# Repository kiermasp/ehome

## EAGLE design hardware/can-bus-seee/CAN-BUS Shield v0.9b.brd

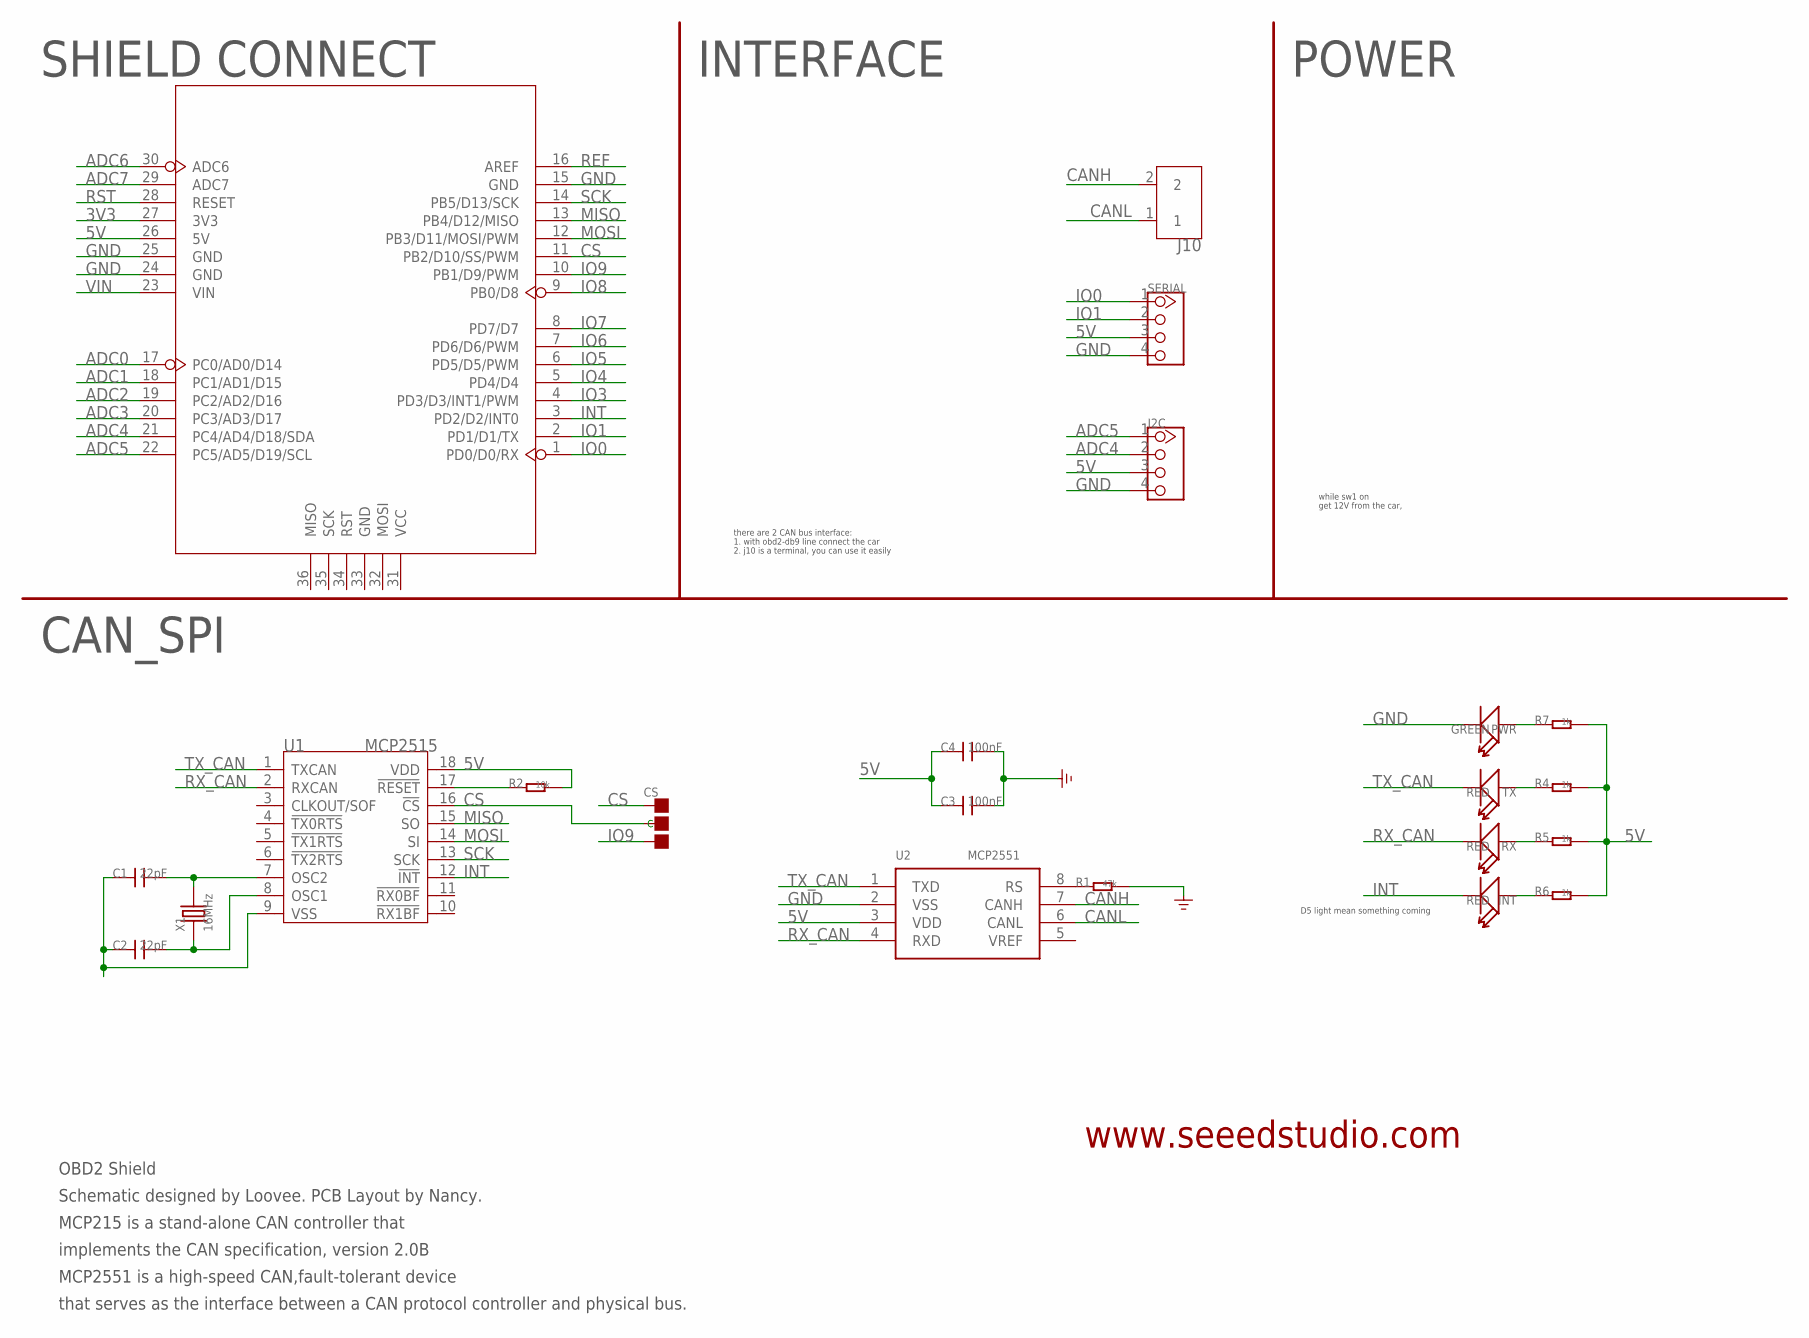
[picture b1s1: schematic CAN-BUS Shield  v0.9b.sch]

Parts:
C1, C2: 22pF; 0603
C3, C4: 100nF; 0603
CS: PAD-JUMPER-3P-40*40; 3P-SMD-4.1X1.5
I2C: TWIG-4P-2.0-2.0; 4P-2.0
INT: RED; LED-0603
J10: SCREW-TERMINAL-2P5.0; 2P-5.0
PWR: GREEN; LED-0603
R1: 47k; 0603
R2: 10k; 0603
R4, R5, R6, R7: 1k; 0603
RX: RED; LED-0603
SERIAL: TWIG-4P-2.0-2.0; 4P-2.0
TX: RED; LED-0603
U1: MCP2515; SOIC18
U2: MCP2551; SO08
U3: ARDUINO
X1: 16MHz; HC49/S

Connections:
3V3: U3.27 (3V3)
5V: C3.1, C4.1, I2C.3, R2.2, R4.2, R5.2, R6.2, R7.2, SERIAL.3, U1.18 (VDD), U2.3 (VDD), U3.26 (5V)
ADC0: U3.17 (PC0/AD0/D14)
ADC1: U3.18 (PC1/AD1/D15)
ADC2: U3.19 (PC2/AD2/D16)
ADC3: U3.20 (PC3/AD3/D17)
ADC4: I2C.2, U3.21 (PC4/AD4/D18/SDA)
ADC5: I2C.1, U3.22 (PC5/AD5/D19/SCL)
ADC6: U3.30 (ADC6)
ADC7: U3.29 (ADC7)
CANH: J10.2, U2.7 (CANH)
CANL: J10.1, U2.6 (CANL)
CS: CS.00 (L), CS.MM (C), U1.16 (!CS), U3.11 (PB2/D10/SS/PWM)
INT: INT.-, U1.12 (!INT), U3.3 (PD2/D2/INT0)
IO0: SERIAL.1, U3.1 (PD0/D0/RX)
IO1: SERIAL.2, U3.2 (PD1/D1/TX)
IO3: U3.4 (PD3/D3/INT1/PWM)
IO4: U3.5 (PD4/D4)
IO5: U3.6 (PD5/D5/PWM)
IO6: U3.7 (PD6/D6/PWM)
IO7: U3.8 (PD7/D7)
IO8: U3.9 (PB0/D8)
IO9: CS.11 (R), U3.10 (PB1/D9/PWM)
MISO: U1.15 (SO), U3.13 (PB4/D12/MISO)
MOSI: U1.14 (SI), U3.12 (PB3/D11/MOSI/PWM)
unnamed: PWR.+, R7.1
unnamed: R4.1, TX.+
unnamed: R5.1, RX.+
unnamed: C1.2, U1.7 (OSC2), X1.2
unnamed: C2.2, U1.8 (OSC1), X1.1
unnamed: INT.+, R6.1
unnamed: R1.1, U2.8 (RS)
REF: U3.16 (AREF)
RST: U3.28 (RESET)
RST_N: R2.1, U1.17 (!RESET)
RX_CAN: RX.-, U1.2 (RXCAN), U2.4 (RXD)
SCK: U1.13 (SCK), U3.14 (PB5/D13/SCK)
TX_CAN: TX.-, U1.1 (TXCAN), U2.1 (TXD)
VIN: U3.23 (VIN)

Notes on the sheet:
CAN_SPI
SHIELD CONNECT
INTERFACE
POWER
get 12V from the car,
D5 light mean something coming
OBD2 Shield
Schematic designed by Loovee. PCB Layout by Nancy.
MCP215 is a stand-alone CAN controller that
MCP2551 is a high-speed CAN,fault-tolerant device
that serves as the interface between a CAN protocol controller and physical bus.
implements the CAN specification, version 2.0B
www.seeedstudio.com
while sw1 on
there are 2 CAN bus interface:
1. with obd2-db9 line connect the car
2. j10 is a terminal, you can use it easily

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
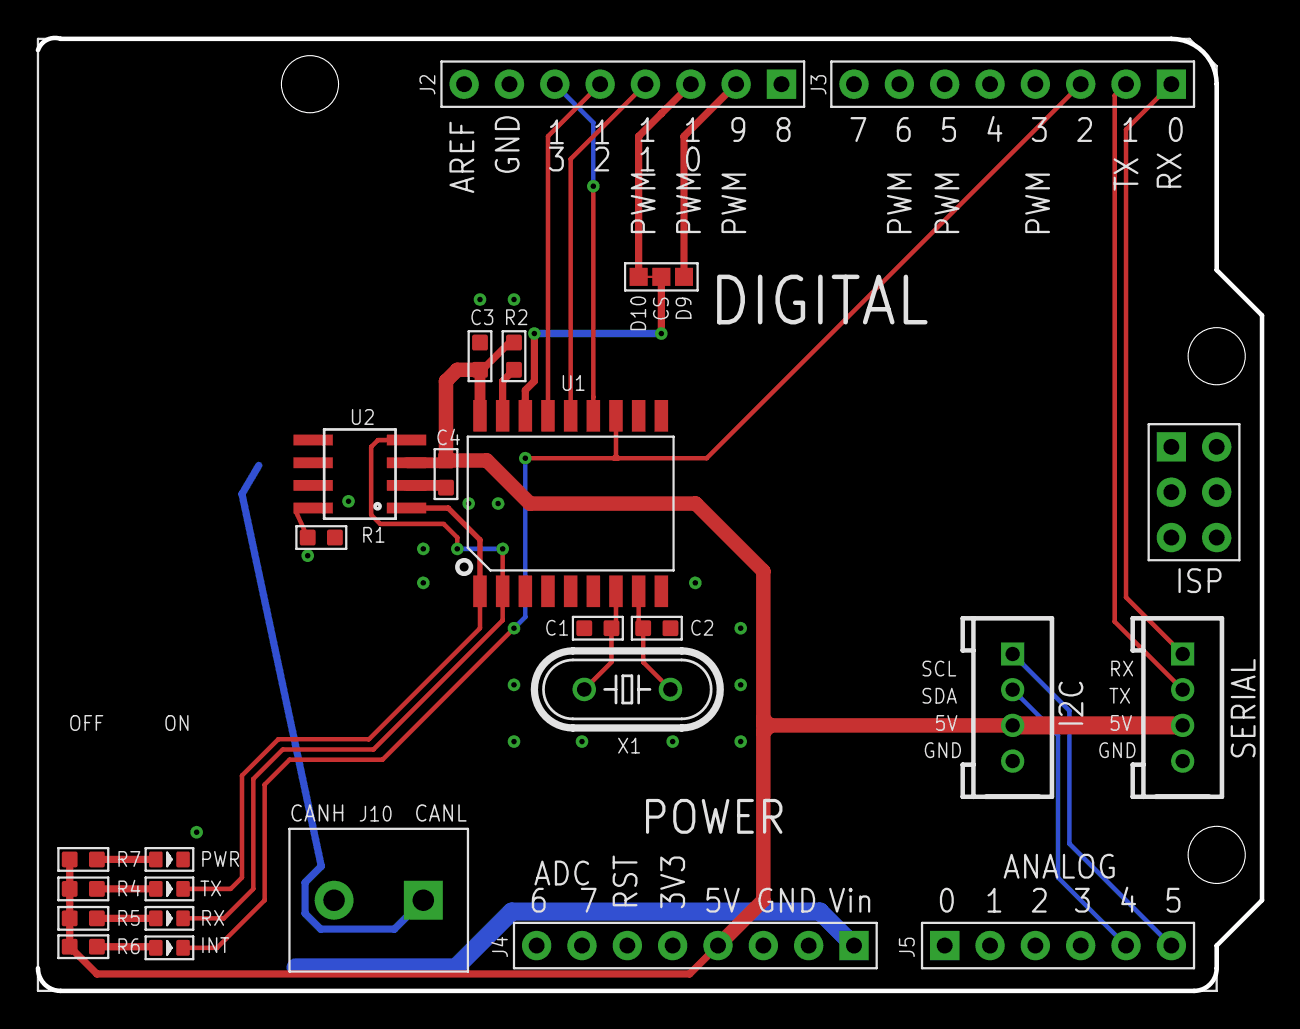
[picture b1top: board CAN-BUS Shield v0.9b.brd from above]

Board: 2 copper layers, 68.6 x 53.4 mm, 22 parts (0 on the bottom side), 24 nets.

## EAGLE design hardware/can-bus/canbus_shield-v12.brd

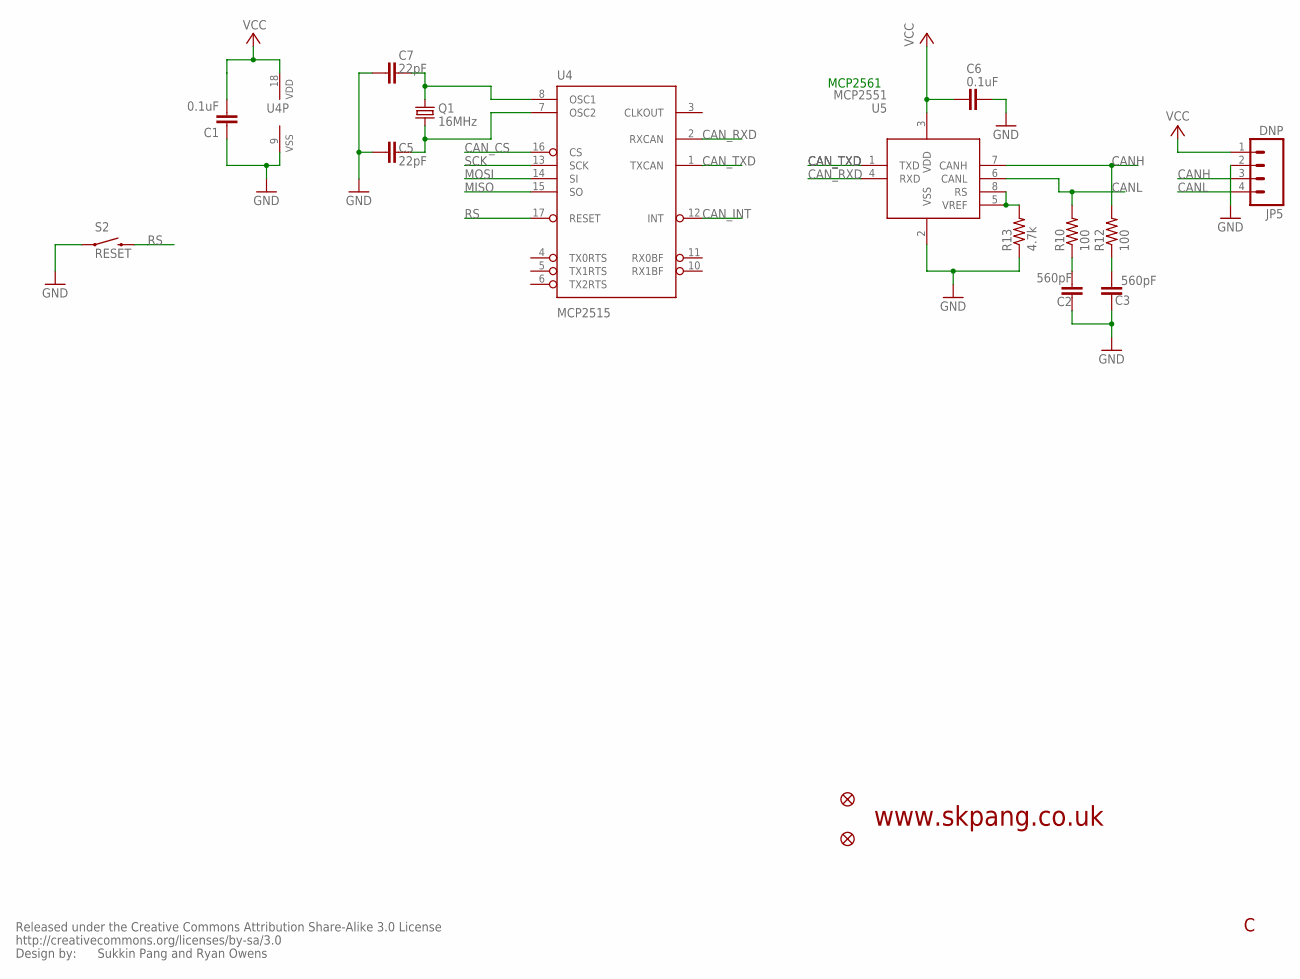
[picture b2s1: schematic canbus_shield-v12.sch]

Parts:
C1, C6: 0.1uF; 0603-CAP
C2, C3: 560pF; 0603-CAP
C5, C7: 22pF; 0603-CAP
JP2, JP3: FIDUCIAL1X2; FIDUCIAL-1X2
JP5: DNP; 1X04
Q1: 16MHz; CRYSTAL-SMD-5X3
R10, R12: 100; 0603-RES
R13: 4.7k; 0603-RES
S2: RESET; TACTILE_SWITCH_SMD
U4: MCP2515; SO-18W
U5: MCP2551; SO-08M
U$1: CREATIVE_COMMONS

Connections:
CANH: JP5.3, R12.2, U5.7 (CANH)
CANL: JP5.4, R10.2, U5.6 (CANL)
CAN_CS: U4.16 (CS)
CAN_INT: U4.12 (INT)
CAN_RXD: U4.2 (RXCAN), U5.4 (RXD)
CAN_TXD: U4.1 (TXCAN), U5.1 (TXD)
GND: C1.1, C2.1, C3.1, C5.1, C6.1, C7.1, JP5.2, R13.1, S2.1, U4.9 (VSS), U5.2 (VSS)
MISO: U4.15 (SO)
MOSI: U4.14 (SI)
unnamed: C2.2, R10.1
unnamed: C3.2, R12.1
unnamed: R13.2, U5.5 (VREF), U5.8 (RS)
unnamed: C7.2, Q1.3 (2), U4.8 (OSC1)
unnamed: C5.2, Q1.1, U4.7 (OSC2)
RS: S2.3 (2), U4.17 (RESET)
SCK: U4.13 (SCK)
VCC: C1.2, C6.2, JP5.1, U4.18 (VDD), U5.3 (VDD)

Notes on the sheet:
www.skpang.co.uk
Sukkin Pang and Ryan Owens
MCP2561

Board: 2 copper layers, 17 parts (0 on the bottom side), 12 nets, no tracks yet.

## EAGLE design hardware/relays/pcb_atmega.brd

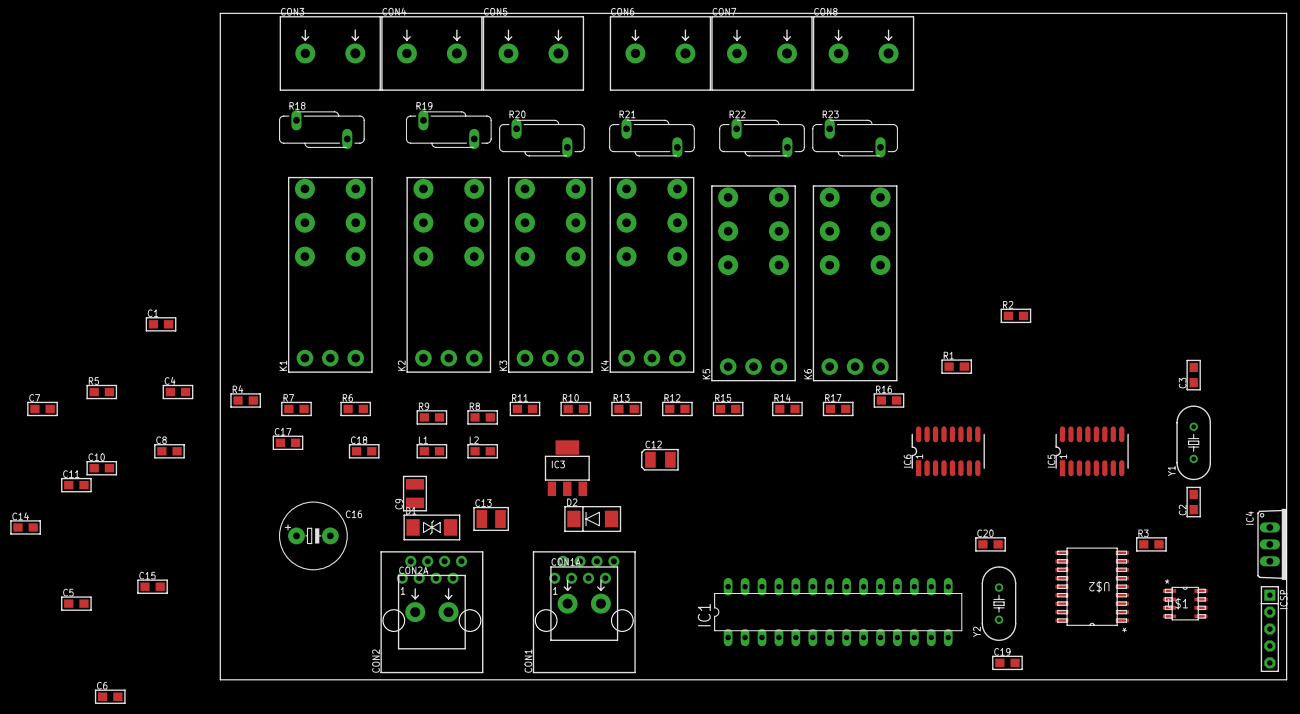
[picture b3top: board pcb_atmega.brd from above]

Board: 2 copper layers, 160.0 x 100.0 mm, 73 parts (0 on the bottom side), 47 nets, no tracks yet.

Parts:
C1, C5, C6, C7, C8, C10, C11, C14, C15, C17, C18: 100n; 0805
C2, C3, C19, C20: 22p; 0805
C4: 10u/6V; 0805
C9, C13: 10u/50V; 1210
C12: 10u/6V; SMC_B
C16: 1000u/16V; CAP-5X10.5
CON1, CON2: RJ45-PCB-SOCKET
CON1A, CON2A: TERMINAL-2; ARK2-5X10,5MM
CON3, CON4, CON5, CON6, CON7, CON8: TERMINAL-2; ARK2-7.5X10.5MM
D1: P6SMB33CA; DO-214_TRANSIL2
D2: S1D; DO-214
IC1: MEGA8-P; DIL28-3
IC3: MCP1790; SOT-223
IC4: 7812; TO220V
IC5, IC6: ULN2003; SO-16
ICSP: SIP-5
K1, K2, K3, K4, K5, K6: RELAY_RT
L1, L2: BLM21A102SPT; 0805
R1: 10k; 0805
R2: 470R; 0805
R3: 4k7; 0805
R4: 51k 1%; 0805
R5: 10k 1%; 0805
R6, R7, R8, R9, R10, R11, R12, R13, R14, R15, R16, R17: 75R; 0805
R18, R19, R20, R21, R22, R23: VAR10-250; S10K
U$1: MCP2551_X_SN; SOIC8_N_MC
U$2: MCP2515_X_SO; SOIC18_W_MC
Y1, Y2: 8MHz; HC49/S

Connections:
+5V: C5.1, C6.1, C11.1, C12.+, IC1.7, IC3.3, ICSP.2, R1.1, U$1.3
+12V: C15.1, C16.+, C17.2, C18.2, IC4.3, IC5.9, IC6.9, R6.1, R7.1, R8.1, R9.1, R10.1, R11.1, R12.1, R13.1, R14.1, R15.1, R16.1, R17.1
GND: C1.2, C2.2, C3.2, C4.2, C5.2, C6.2, C7.2, C8.2, C9.2, C10.2, C11.2, C12.-, C13.2, C14.2, C15.2, C16.-, C17.1, C18.1, C19.2, C20.2, CON1.5, CON1.7, CON2.5, CON2.7, CON2A.1, D1.C, IC1.8, IC1.22, IC3.2, IC3.4, IC4.2, IC5.8, IC6.8, ICSP.3, R3.1, R5.1, U$1.2
K1A1: IC5.16, K1.A1, R6.2
K1A2: IC6.16, K1.A2, R7.2
K2A1: IC5.15, K2.A1, R8.2
K2A2: IC6.15, K2.A2, R9.2
K3A1: IC5.14, K3.A1, R10.2
K3A2: IC6.14, K3.A2, R11.2
K4A1: IC5.13, K4.A1, R12.2
K4A2: IC6.13, K4.A2, R13.2
K5A1: IC5.12, K5.A1, R14.2
K5A2: IC6.12, K5.A2, R15.2
K6A1: IC5.11, K6.A1, R16.2
K6A2: IC6.11, K6.A2, R17.2
unnamed: D2.C, L1.2, L2.2
unnamed: U$1.4, U$2.1
unnamed: U$1.1, U$2.2
unnamed: CON1.1, CON1A.2, CON2.1
unnamed: C9.1, C10.1, IC3.1, L1.1, R4.1
unnamed: C13.1, C14.1, IC4.1, L2.1
unnamed: C1.1, R1.2, R2.1
unnamed: IC1.1, ICSP.1, R2.2
unnamed: C8.1, CON1.4, CON1.8, CON2.4, CON2.8, CON2A.2, D1.A, D2.A
unnamed: IC1.19, U$2.13
unnamed: IC1.18, U$2.15
unnamed: R3.2, U$1.5, U$1.6, U$1.7, U$1.8
unnamed: C7.1, R4.2, R5.2
unnamed: IC1.17, U$2.14
unnamed: C3.1, IC1.10, Y1.2
unnamed: IC1.16, U$2.16
unnamed: C20.1, U$2.8, Y2.2
unnamed: C19.1, U$2.7, Y2.1
unnamed: CON1.2, CON1A.1, CON2.2
unnamed: CON3.1, K1.11A, K1.11B, R18.1
unnamed: CON3.2, K1.14A, K1.14B, R18.2
unnamed: C2.1, IC1.9, Y1.1
unnamed: CON4.2, K2.14A, K2.14B, R19.2
unnamed: CON5.2, K3.14A, K3.14B, R20.2
unnamed: CON6.2, K4.14A, K4.14B, R21.2
unnamed: CON7.2, K5.14A, K5.14B, R22.2
unnamed: CON8.2, K6.14A, K6.14B, R23.2
unnamed: CON4.1, K2.11A, K2.11B, R19.1
unnamed: CON5.1, K3.11A, K3.11B, R20.1
unnamed: CON6.1, K4.11A, K4.11B, R21.1
unnamed: CON7.1, K5.11A, K5.11B, R22.1
unnamed: CON8.1, K6.11A, K6.11B, R23.1

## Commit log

2015-02-15 Add first sketch of button project
    * Implement interrupt debounce mechamism
    * Implement switching button
2015-04-06 Add button project
2015-04-06 Create CAN Interface
2015-04-11 Adding new functionality
2015-04-11 Remove unused libraries
2015-04-11 Adding libraries
2015-04-12 Invert order of messages Add enable/disable REG
2015-04-13 Remove unused functions
    Remove getMessage();
    Move fuctions to private:
    * void setNodeId(uint8_t id);
    * void setGroupId(uint8_t id);
    * void setFirmwareId(const void* _src);
2015-04-13 Remove unused functions
2015-04-13 Cleanup for sending messages
2015-04-13 Code cleanup
2015-04-13 Remvoe usless functions
2015-04-13 Fix compiling
2015-05-03 files
2015-05-05 new pdf files
2015-05-11 Add new pdf file

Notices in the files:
parts and their libraries:
SparkFun: Released under the Creative Commons Attribution Share-Alike 3.0 License
SparkFun: http://creativecommons.org/licenses/by-sa/3.0
